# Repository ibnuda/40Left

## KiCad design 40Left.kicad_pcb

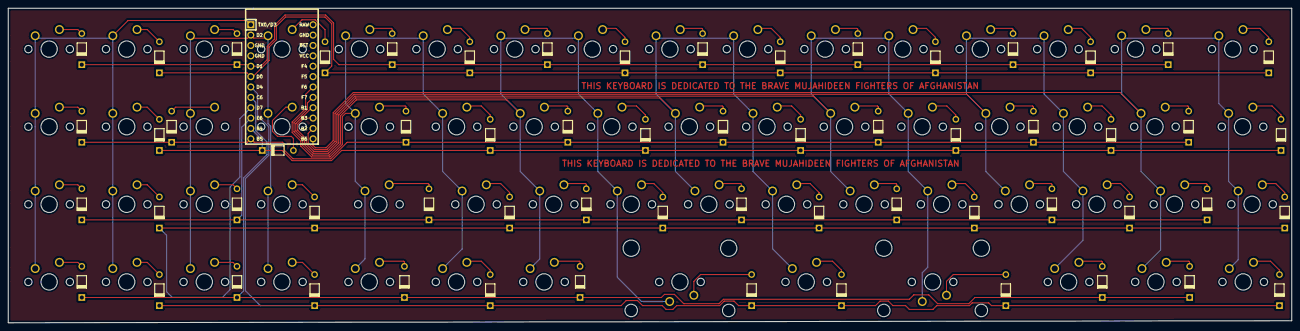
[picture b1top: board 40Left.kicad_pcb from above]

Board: 2 copper layers, 314.2 x 77.0 mm, 123 parts (0 on the bottom side), 77 nets.

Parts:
D1, D2, D3, D4, D5, D6, D7, D8, D9, D10, D11, D12, D13, D14, D15, D16, D17, D18, D19, D20, D21, D22, D23, D24, D25, D26, D27, D28, D29, D30, D31, D32, D33, D34, D35, D37, D38, D39, D40, D41, D42, D43, D45, D46, D47, D48, D49, D50, D51, D52, D53, D54, D55, D57, D58, D59, D60, D61, D62, D63, D64: D; diode
SW1, SW2, SW3, SW4, SW5, SW6, SW7, SW8, SW9, SW10, SW11, SW12, SW13, SW14, SW15, SW16, SW17, SW21, SW22, SW23, SW24, SW25, SW26, SW27, SW29, SW30, SW31, SW33, SW34, SW35, SW37, SW38, SW39, SW40, SW41, SW42, SW43, SW45, SW46, SW47, SW49, SW50, SW51, SW53, SW54, SW55, SW57, SW58, SW59, SW60, SW63: SW_PUSH; 100-minimal
SW18, SW20, SW28, SW52, SW62, SW64: SW_PUSH; 125-minimal
SW19, SW61: SW_PUSH; 150-minimal
SW32, SW48: SW_PUSH; 225-minimal
U1: ProMicro; promicro

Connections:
C01: SW1.1, SW2.1, SW3.1, SW4.1, SW5.1, SW6.1, SW7.1, SW8.1, U1.1
C23: SW9.1, SW10.1, SW11.1, SW12.1, SW13.1, SW14.1, SW15.1, SW16.1, U1.2
C45: SW17.1, SW18.1, SW19.1, SW20.1, SW21.1, SW22.1, SW23.1, SW24.1, U1.18
C67: SW25.1, SW26.1, SW27.1, SW28.1, SW29.1, SW30.1, SW31.1, SW32.2, U1.17
C89: SW33.1, SW34.1, SW35.1, SW37.1, SW38.1, SW39.1, SW40.1, U1.16
CAB: SW41.1, SW42.1, SW43.1, SW45.1, SW46.1, SW47.1, SW48.2, U1.15
CCD: SW49.1, SW50.1, SW51.1, SW52.1, SW53.1, SW54.1, SW55.1, U1.14
CEF: SW57.1, SW58.1, SW59.1, SW60.1, SW61.1, SW62.1, SW63.1, SW64.1, U1.13
unnamed: D1.2, SW1.2
unnamed: D2.2, SW2.2
unnamed: D3.2, SW3.2
unnamed: D4.2, SW4.2
unnamed: D5.2, SW5.2
unnamed: D6.2, SW6.2
unnamed: D7.2, SW7.2
unnamed: D8.2, SW8.2
unnamed: D9.2, SW9.2
unnamed: D10.2, SW10.2
unnamed: D11.2, SW11.2
unnamed: D12.2, SW12.2
unnamed: D13.2, SW13.2
unnamed: D14.2, SW14.2
unnamed: D15.2, SW15.2
unnamed: D16.2, SW16.2
unnamed: D17.2, SW17.2
unnamed: D18.2, SW18.2
unnamed: D19.2, SW19.2
unnamed: D20.2, SW20.2
unnamed: D21.2, SW21.2
unnamed: D22.2, SW22.2
unnamed: D23.2, SW23.2
unnamed: D24.2, SW24.2
unnamed: D25.2, SW25.2
unnamed: D26.2, SW26.2
unnamed: D27.2, SW27.2
unnamed: D28.2, SW28.2
unnamed: D29.2, SW29.2
unnamed: D30.2, SW30.2
unnamed: D31.2, SW31.2
unnamed: D32.2, SW32.1
unnamed: D33.2, SW33.2
unnamed: D34.2, SW34.2
unnamed: D35.2, SW35.2
unnamed: D37.2, SW37.2
unnamed: D38.2, SW38.2
unnamed: D39.2, SW39.2
unnamed: D40.2, SW40.2
unnamed: D41.2, SW41.2
unnamed: D42.2, SW42.2
unnamed: D43.2, SW43.2
unnamed: D45.2, SW45.2
unnamed: D46.2, SW46.2
unnamed: D47.2, SW47.2
unnamed: D48.2, SW48.1
unnamed: D49.2, SW49.2
unnamed: D50.2, SW50.2
unnamed: D51.2, SW51.2
unnamed: D52.2, SW52.2
unnamed: D53.2, SW53.2
unnamed: D54.2, SW54.2
unnamed: D55.2, SW55.2
unnamed: D57.2, SW57.2
unnamed: D58.2, SW58.2
unnamed: D59.2, SW59.2
unnamed: D60.2, SW60.2
unnamed: D61.2, SW61.2
unnamed: D62.2, SW62.2
unnamed: D63.2, SW63.2
unnamed: D64.2, SW64.2
R0A: D1.1, D9.1, D17.1, D25.1, D33.1, D41.1, D49.1, D57.1, U1.5
R0B: D5.1, D13.1, D21.1, D29.1, D37.1, D45.1, D53.1, D61.1, U1.6
R1A: D2.1, D10.1, D18.1, D26.1, D34.1, D42.1, D50.1, D58.1, U1.12
R1B: D6.1, D14.1, D22.1, D30.1, D38.1, D46.1, D54.1, D62.1, U1.11
R2A: D3.1, D11.1, D19.1, D27.1, D35.1, D43.1, D51.1, D59.1, U1.10
R2B: D7.1, D15.1, D23.1, D31.1, D39.1, D47.1, D55.1, D63.1, U1.9
R3A: D4.1, D12.1, D20.1, D28.1, D52.1, D60.1, U1.8
R3B: D8.1, D16.1, D24.1, D32.1, D40.1, D48.1, D64.1, U1.7

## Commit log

2019-12-22 init commit.
2019-12-22 smh my head famalamadingdong.
2021-11-17 removed libs.
2021-11-17 updated the footprint.
2021-11-17 updated the readme to reflect the real situation.
2021-12-08 shorter.
